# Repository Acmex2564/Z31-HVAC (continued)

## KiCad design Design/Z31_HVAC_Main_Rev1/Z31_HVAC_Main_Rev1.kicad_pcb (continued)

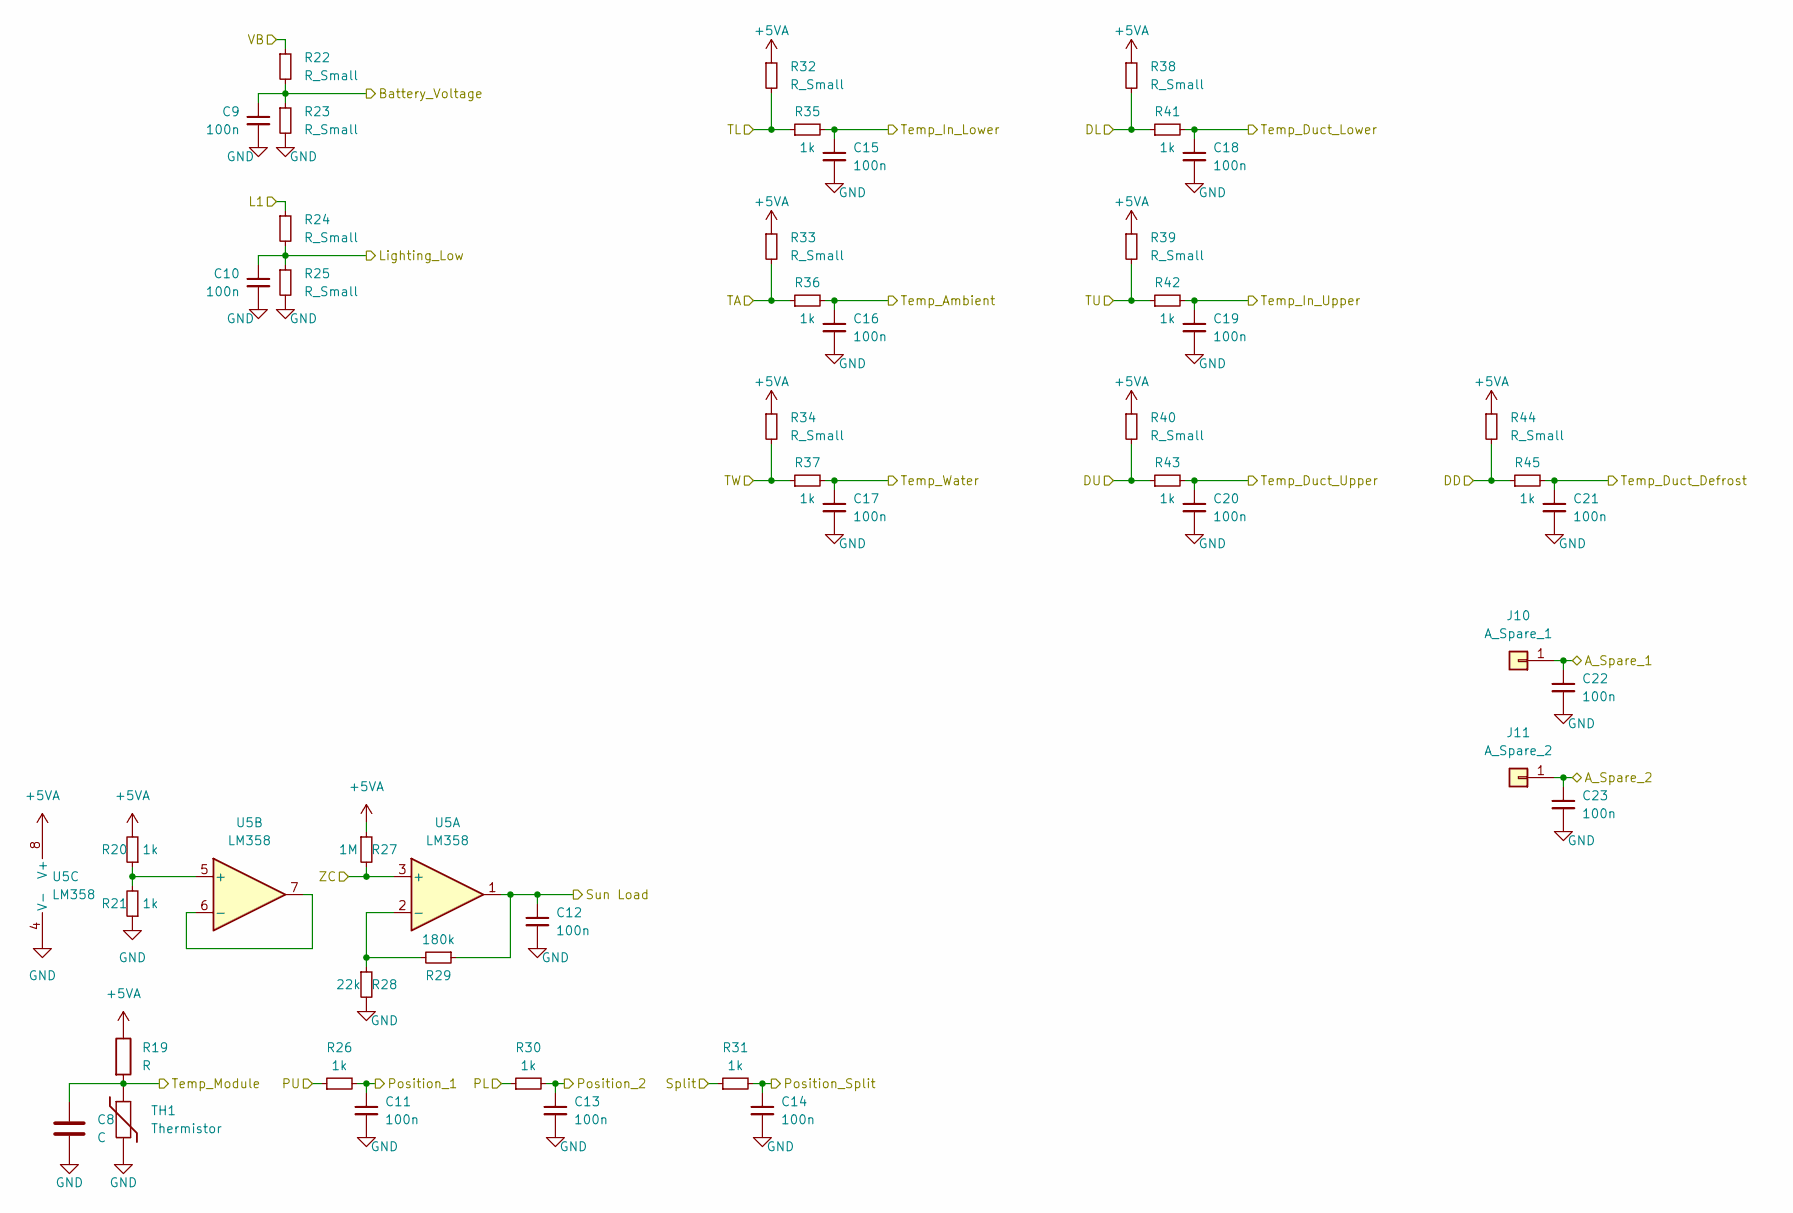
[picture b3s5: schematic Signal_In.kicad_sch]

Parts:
C8: C; C_0805_2012Metric_Pad1.18x1.45mm_HandSolder
C9, C10, C11, C12, C13, C14, C15, C16, C17, C18, C19, C20, C21, C22, C23: 100n; C_0805_2012Metric_Pad1.18x1.45mm_HandSolder
J10: A_Spare_1; PinHeader_1x01_P2.54mm_Vertical
J11: A_Spare_2; PinHeader_1x01_P2.54mm_Vertical
R19: R; R_0805_2012Metric_Pad1.20x1.40mm_HandSolder
R20, R21, R26, R30, R31, R35, R36, R37, R41, R42, R43, R45: 1k; R_0805_2012Metric_Pad1.20x1.40mm_HandSolder
R22, R23, R24, R25: R_Small; R_0805_2012Metric_Pad1.20x1.40mm_HandSolder
R27: 1M; R_Axial_DIN0207_L6.3mm_D2.5mm_P10.16mm_Horizontal
R28: 22k; R_0805_2012Metric_Pad1.20x1.40mm_HandSolder
R29: 180k; R_0805_2012Metric_Pad1.20x1.40mm_HandSolder
R32, R33, R34, R38, R39, R40, R44: R_Small; R_Axial_DIN0207_L6.3mm_D2.5mm_P10.16mm_Horizontal
TH1: Thermistor; R_0805_2012Metric_Pad1.20x1.40mm_HandSolder
U5: LM358; SO-8_5.3x6.2mm_P1.27mm

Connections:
+5VA: R19.1, R20.2, R27.1, R32.1, R33.1, R34.1, R38.1, R39.1, R40.1, R44.1, U5.8 (V+); also elsewhere on the board
+12V: R22.1; also elsewhere on the board
/DD: R44.2, R45.1; also elsewhere on the board
/DL: R38.2, R41.1; also elsewhere on the board
/DU: R40.2, R43.1; also elsewhere on the board
/L1: R24.1; also elsewhere on the board
/PL: R30.1; also elsewhere on the board
/PU: R26.1; also elsewhere on the board
/Signal_In (Analog)/A_Spare_1: C22.1, J10.1; also elsewhere on the board
/Signal_In (Analog)/A_Spare_2: C23.1, J11.1; also elsewhere on the board
/Signal_In (Analog)/Battery_Voltage: C9.1, R22.2, R23.1; also elsewhere on the board
/Signal_In (Analog)/Lighting_Low: C10.1, R24.2, R25.1; also elsewhere on the board
/Signal_In (Analog)/Position_1: C11.1, R26.2; also elsewhere on the board
/Signal_In (Analog)/Position_2: C13.1, R30.2; also elsewhere on the board
/Signal_In (Analog)/Position_Split: C14.1, R31.2; also elsewhere on the board
/Signal_In (Analog)/Sun Load: C12.1, R29.1, U5.1; also elsewhere on the board
/Signal_In (Analog)/Temp_Ambient: C16.1, R36.2; also elsewhere on the board
/Signal_In (Analog)/Temp_Duct_Defrost: C21.1, R45.2; also elsewhere on the board
/Signal_In (Analog)/Temp_Duct_Lower: C18.1, R41.2; also elsewhere on the board
/Signal_In (Analog)/Temp_Duct_Upper: C20.1, R43.2; also elsewhere on the board
/Signal_In (Analog)/Temp_In_Lower: C15.1, R35.2; also elsewhere on the board
/Signal_In (Analog)/Temp_In_Upper: C19.1, R42.2; also elsewhere on the board
/Signal_In (Analog)/Temp_Module: C8.1, R19.2, TH1.1; also elsewhere on the board
/Signal_In (Analog)/Temp_Water: C17.1, R37.2; also elsewhere on the board
/TA: R33.2, R36.1; also elsewhere on the board
/TL: R32.2, R35.1; also elsewhere on the board
/TU: R39.2, R42.1; also elsewhere on the board
/TW: R34.2, R37.1; also elsewhere on the board
/Temp_Adjustment: R31.1; also elsewhere on the board
/ZC: R27.2, U5.3 (+); also elsewhere on the board
GND: C8.2, C9.2, C10.2, C11.2, C12.2, C13.2, C14.2, C15.2, C16.2, C17.2, C18.2, C19.2, C20.2, C21.2, C22.2, C23.2, R21.1, R23.2, R25.2, R28.2, TH1.2, U5.4 (V-); also elsewhere on the board
unnamed: R20.1, R21.2, U5.5 (+)
unnamed: R28.1, R29.2, U5.2 (-)
unnamed: U5.6 (-), U5.7

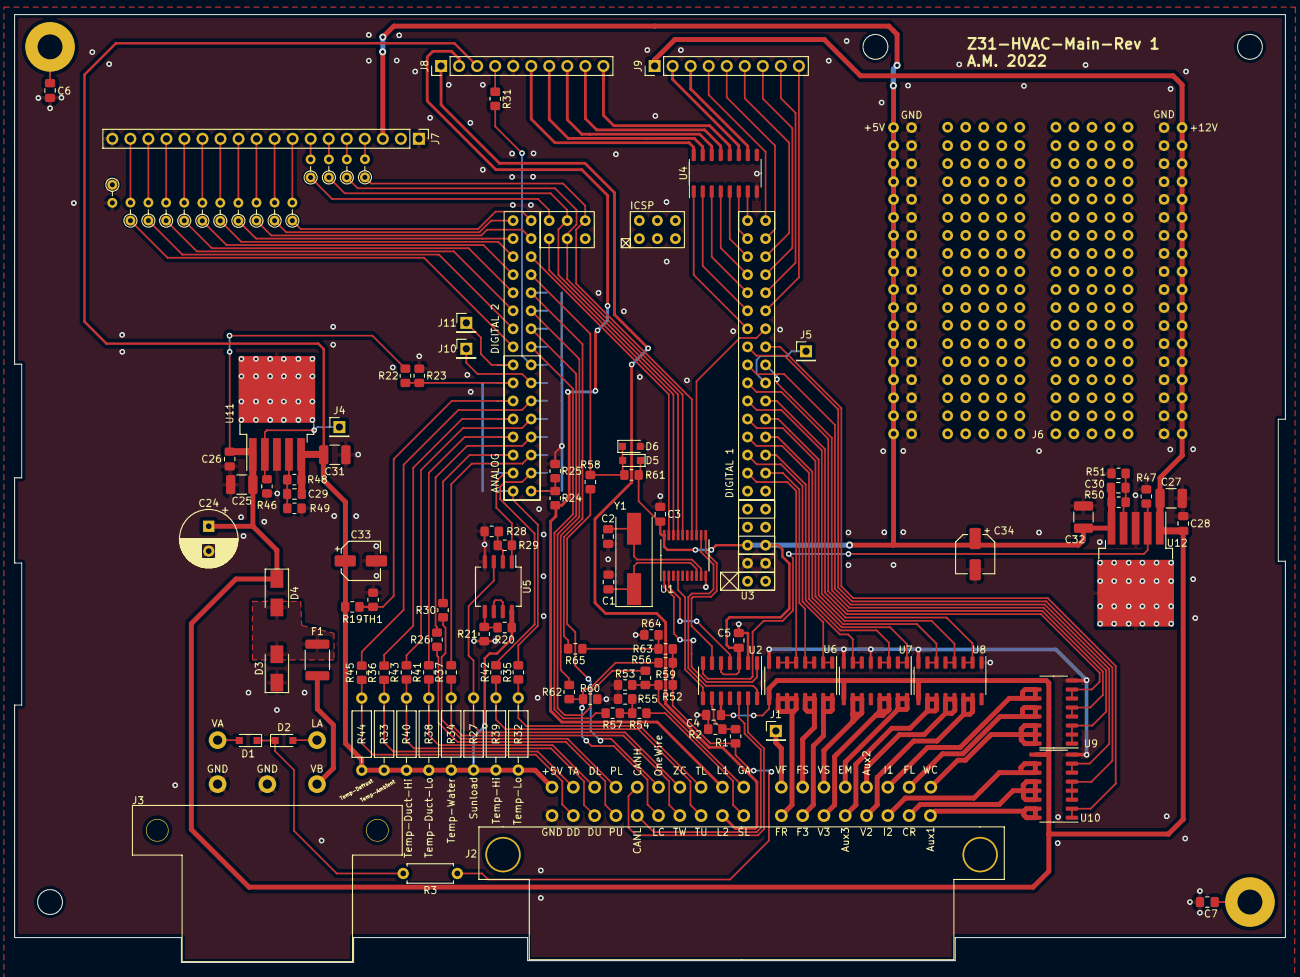
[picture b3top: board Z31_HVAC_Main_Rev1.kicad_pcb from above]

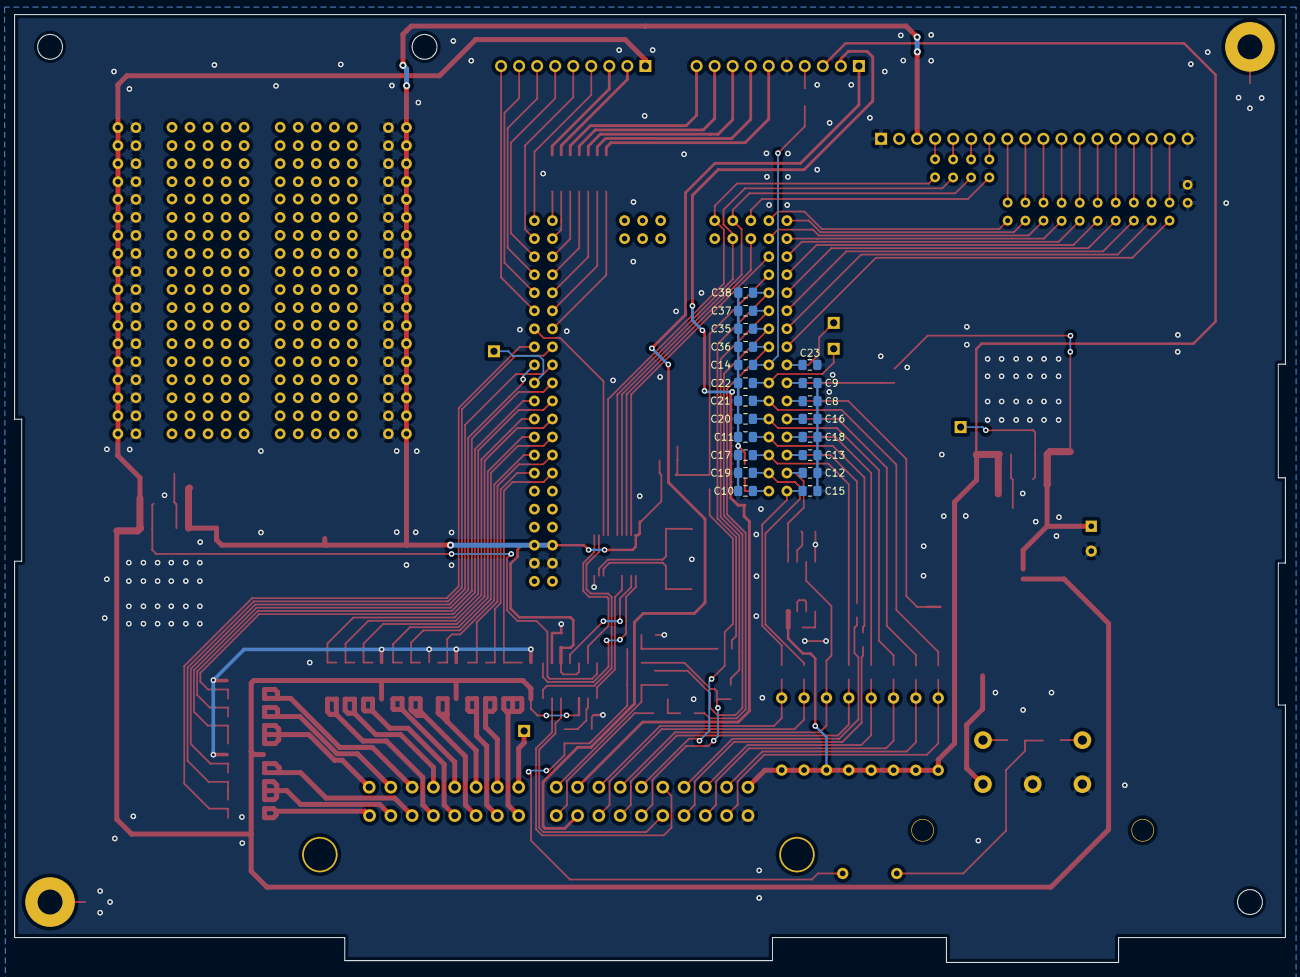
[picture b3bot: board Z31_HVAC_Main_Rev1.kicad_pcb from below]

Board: 2 copper layers, 179.0 x 133.5 mm, 137 parts (20 on the bottom side), 152 nets.

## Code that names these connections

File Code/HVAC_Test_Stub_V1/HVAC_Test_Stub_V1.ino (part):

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#define LIGHT_AC 28
#define LIGHT_DEMIST 30

#define KEY_ROW_1 31
#define KEY_ROW_2 29
#define KEY_ROW_3 25
#define KEY_ROW_4 21
#define KEY_COL_1 27
#define KEY_COL_2 23

#define IN_TEMP_LOWER A0
#define IN_ILLUM_BRIGHTNESS A1
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                          {'A', 'M'} //Auto, DeMist
                        };

byte rowPins[rows] = {KEY_ROW_1, KEY_ROW_2, KEY_ROW_3, KEY_ROW_4};
byte colPins[cols] = {KEY_COL_1, KEY_COL_2};
Keypad buttons = Keypad(makeKeymap(keys), rowPins, colPins, rows, cols);

//struct sTemp
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
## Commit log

2021-12-23 add pinout data
2021-12-24 lkjhhj
2021-12-24 upgrade file versions
2021-12-26 update to kicad-6
2021-12-28 afasdf
2022-04-08 large changes
2022-04-08 add sub sheets
2022-09-29 Catchup Commit
2022-10-23 Include debug print statements in mixdoor adjustment
2022-10-23 Fix ' to " and strike errant ' in #includes
2022-12-22 Add exponential curve for temperature sensors
2022-12-22 Catchup commit idk
2023-01-07 Fix endlessly cycling mix door positions (probably)
2023-01-07 Decrease mix door service frequency
2023-01-07 Add debug statement for mix door position
2023-01-07 Increase mix door adjustment frequency Remove CAN temperature debug print
2023-01-08 Backup plan for leaking lower door actuator
